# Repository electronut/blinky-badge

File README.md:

I wanted to create a simple project to teach soldering and electronics
to kids (10+ years) and beginners. I first thought of a simple two
transistor LED flasher, but then decided to make it interactive by
adding a touch sensitive element to it. The idea is that once made,
this PCB can be worn as a badge.

I had initially designed this using through-hole components. But with
SMD becoming more and more common, it seems like a better choice. Plus
SMD will have a much flatter profile - more suited to a badge.

I plan to test this out with my 10-year old first. If that goes well,
I plan to organize a soldering workshop in my neighborhood.

# License

<br /><span xmlns:dct="http://purl.org/dc/terms/" property="dct:title">Touch Activated Blinky Badge</span> by <a xmlns:cc="http://creativecommons.org/ns#" href="electronut.in" property="cc:attributionName" rel="cc:attributionURL">Mahesh Venkitachalam</a> is licensed under a <a rel="license" href="http://creativecommons.org/licenses/by/4.0/">Creative Commons Attribution 4.0 International License</a>.

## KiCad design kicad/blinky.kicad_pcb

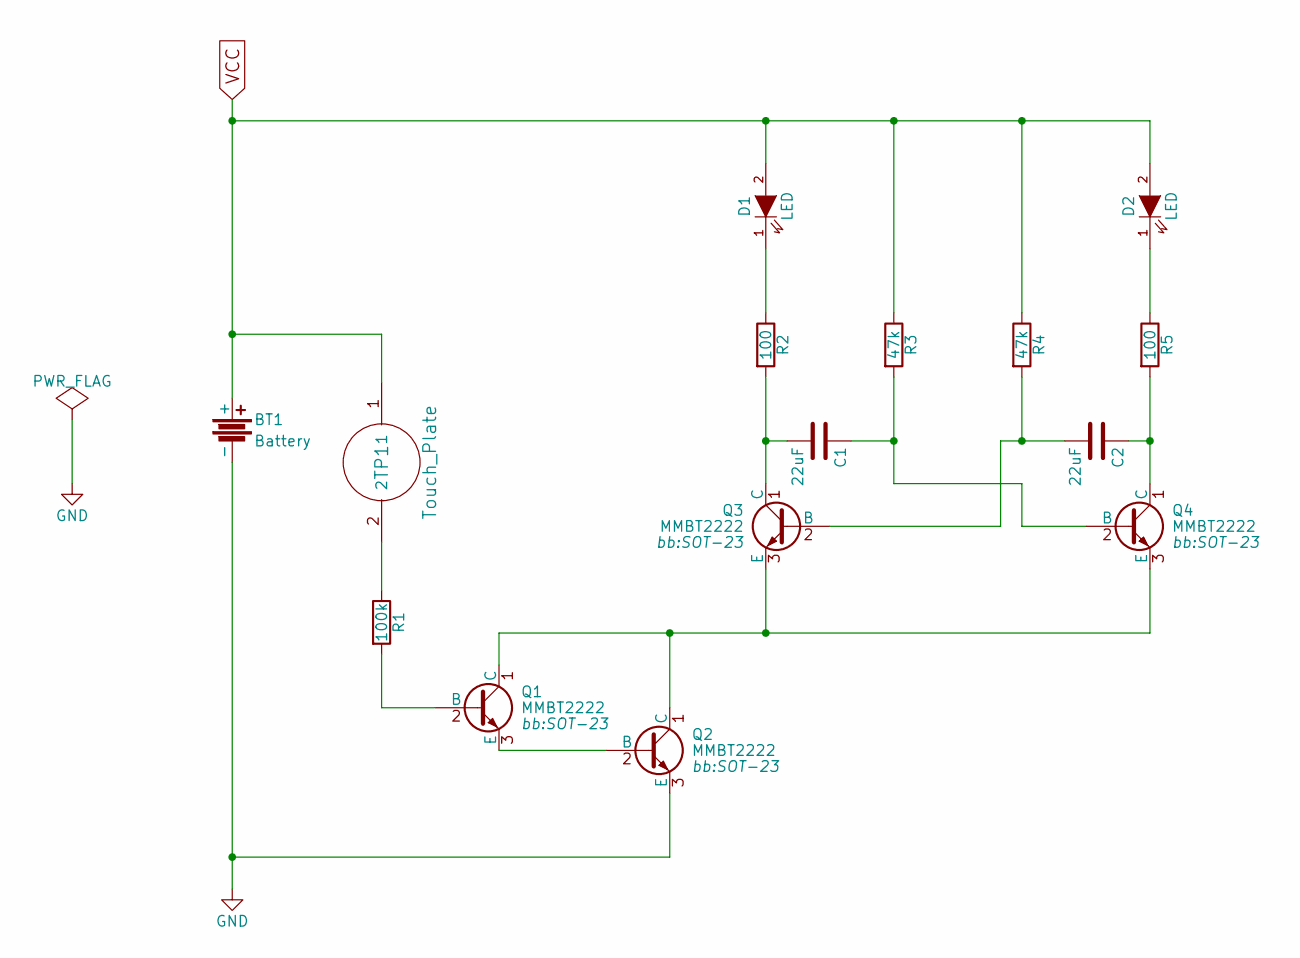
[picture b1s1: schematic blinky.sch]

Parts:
BT1: Battery; CR2032-SMD
C1, C2: 22uF; C_0805_HandSoldering
D1, D2: LED; LED-1206
Q1, Q2, Q3, Q4: MMBT2222; SOT-23
R1: 100k; R_0805_HandSoldering
R2, R5: 100; R_0805_HandSoldering
R3, R4: 47k; R_0805_HandSoldering
TP1: Touch_Plate; TouchPlate-10mm

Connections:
GND: BT1.2 (-), Q2.3 (E)
unnamed: C1.1, Q4.2 (B), R3.2
unnamed: C1.2, Q3.1 (C), R2.2
unnamed: C2.1, Q4.1 (C), R5.2
unnamed: C2.2, Q3.2 (B), R4.2
unnamed: D1.1 (K), R2.1
unnamed: D2.1 (K), R5.1
unnamed: Q1.1 (C), Q2.1 (C), Q3.3 (E), Q4.3 (E)
unnamed: Q1.2 (B), R1.2
unnamed: Q1.3 (E), Q2.2 (B)
unnamed: R1.1, TP1.2
VCC: BT1.1 (+), D1.2 (A), D2.2 (A), R3.1, R4.1, TP1.1

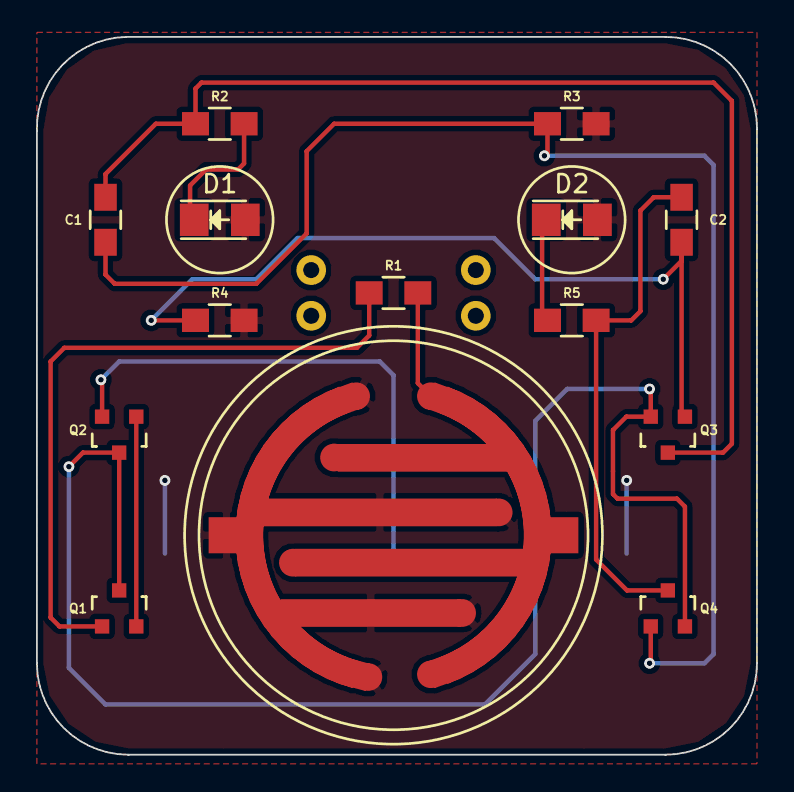
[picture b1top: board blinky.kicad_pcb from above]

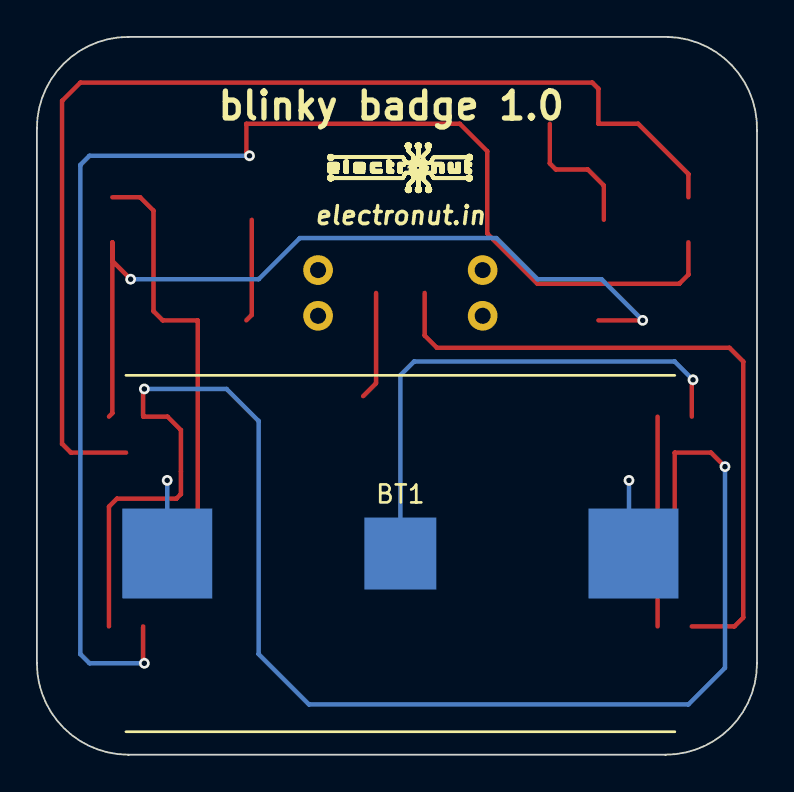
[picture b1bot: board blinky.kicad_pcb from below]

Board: 2 copper layers, 40.0 x 39.9 mm, 18 parts (2 on the bottom side), 12 nets.

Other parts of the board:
J2, J2#2: Val**; H2-2.54
U$2: LOGO; LOGO_electronut

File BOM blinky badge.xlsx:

BOM Blinky Badge
Mahesh Venkitachalam
electronut.in
No. | Reference | Value | Description | Package | Link
1.0 | BT1 | N/A | CR2032 Battery holder | N/A | http://in.element14.com/multicomp/bc-2001/retainer-clip-20mm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
2.0 | C1, C2 | 22uF |  | 0805 | http://in.element14.com/jsp/search/productdetail.jsp?sku=168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
3.0 | D1, D2 | N/A | Red LED | 1206 | http://in.element14.com/jsp/search/productdetail.jsp?sku=209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
4.0 | Q1, Q2, Q3, Q4 | MMBT2222 | Transistor | SOT-23 | http://in.element14.com/jsp/search/productdetail.jsp?sku=105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
5.0 | R1 | 100k |  | 0805 | http://in.element14.com/jsp/search/productdetail.jsp?sku=244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
6.0 | R2, R5 | 100.0 |  | 0805 | http://in.element14.com/multicomp/mcwr08x1000ftl/res-thick-f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
7.0 | R3, R4 | 47k |  | 0805 | http://in.element14.com/jsp/search/productdetail.jsp?sku=244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

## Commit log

2015-09-02 initial
2015-09-04 routing done
2015-09-04 updated gerbers
2015-09-04 added logo
2015-09-04 updated zone fill
2015-09-05 switched to 1206 LEDs
2015-09-25 updated images
2016-01-22 updated with th
